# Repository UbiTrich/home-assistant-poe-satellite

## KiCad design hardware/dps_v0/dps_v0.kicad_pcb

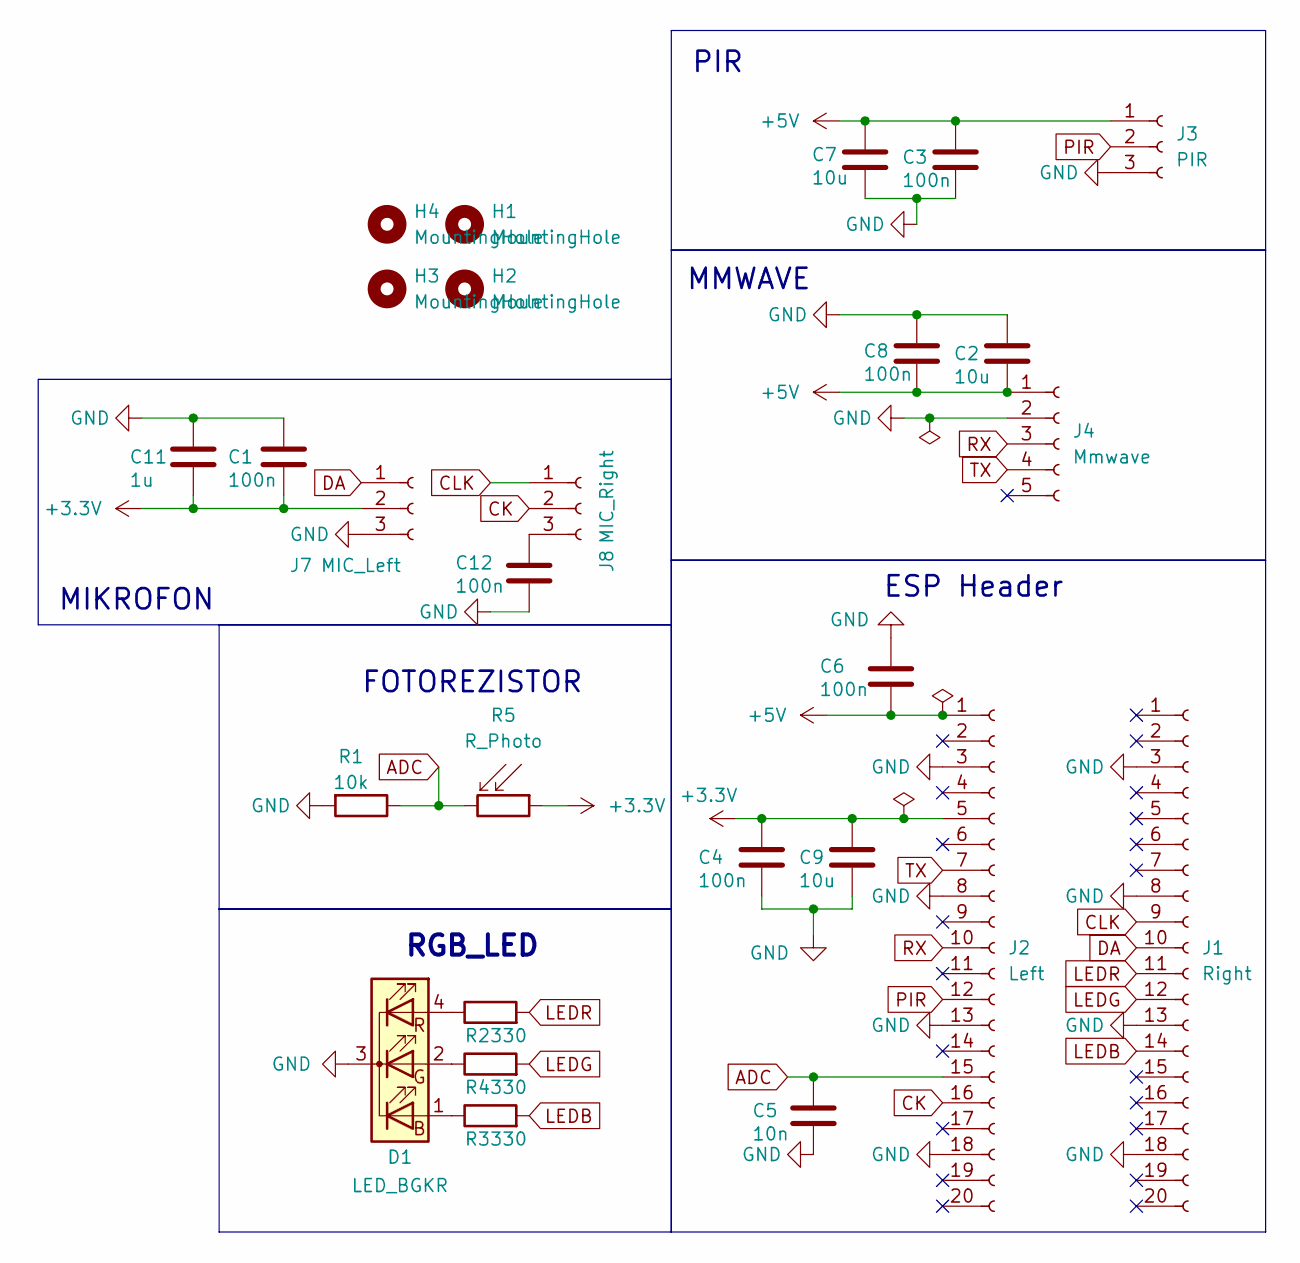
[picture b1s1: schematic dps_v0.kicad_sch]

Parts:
C1, C3, C4, C6, C8, C12: 100n; C_0805_2012Metric_Pad1.18x1.45mm_HandSolder
C2, C7, C9: 10u; C_0805_2012Metric_Pad1.18x1.45mm_HandSolder
C5: 10n; C_0805_2012Metric_Pad1.18x1.45mm_HandSolder
C11: 1u; C_0805_2012Metric_Pad1.18x1.45mm_HandSolder
D1: LED_BGKR; LED_D5.0mm-4_RGB_Wide_Pins
H1, H2, H3, H4: MountingHole; MountingHole_3mm
J1: Right; PinSocket_1x20_P2.54mm_Vertical
J2: Left; PinSocket_1x20_P2.54mm_Vertical
J3: PIR; PinSocket_1x03_P2.54mm_Vertical
J4: Mmwave; PinSocket_1x05_P1.27mm_Vertical
J7: MIC_Left; PinSocket_1x03_P2.54mm_Vertical
J8: MIC_Right; PinSocket_1x03_P2.54mm_Vertical
R1: 10k; R_0805_2012Metric_Pad1.20x1.40mm_HandSolder
R2, R3, R4: 330; R_0805_2012Metric_Pad1.20x1.40mm_HandSolder
R5: R_Photo; R_LDR_5.1x4.3mm_P3.4mm_Vertical

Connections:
+3.3V: C1.1, C4.2, C9.2, C11.1, J2.5, J7.2, R5.1
+5V: C2.1, C3.2, C6.1, C7.2, C8.1, J2.1, J3.1, J4.1
ADC: C5.2, J2.15, R1.1, R5.2
CK: J2.16, J8.2
CLK: J1.9, J8.1
DA: J1.10, J7.1
GND: C1.2, C2.2, C3.1, C4.1, C5.1, C6.2, C7.1, C8.2, C9.1, C11.2, C12.1, D1.3 (K), J1.3, J1.8, J1.13, J1.18, J2.3, J2.8, J2.13, J2.18, J3.3, J4.2, J7.3, R1.2
LEDB: J1.14, R3.2
LEDG: J1.12, R4.2
LEDR: J1.11, R2.2
unnamed: D1.1 (BA), R3.1
unnamed: D1.2 (GA), R4.1
unnamed: D1.4 (RA), R2.1
unnamed: C12.2, J8.3
PIR: J2.12, J3.2
RX: J2.10, J4.3
TX: J2.7, J4.4

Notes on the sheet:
ESP Header
MMWAVE
FOTOREZISTOR
MIKROFON
RGB_LED
PIR

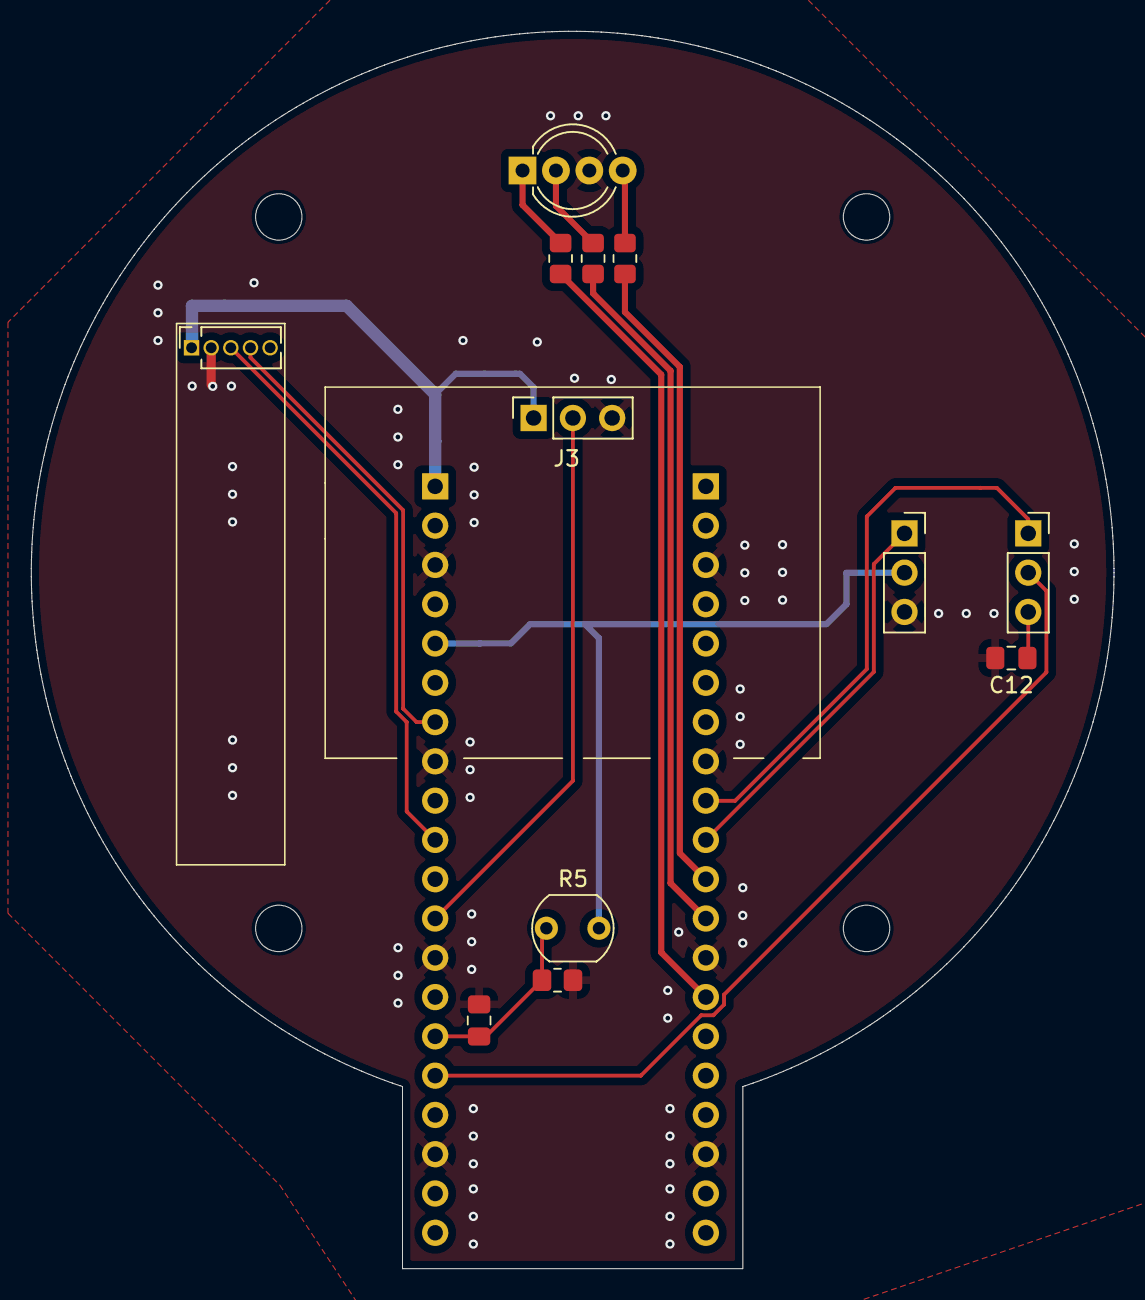
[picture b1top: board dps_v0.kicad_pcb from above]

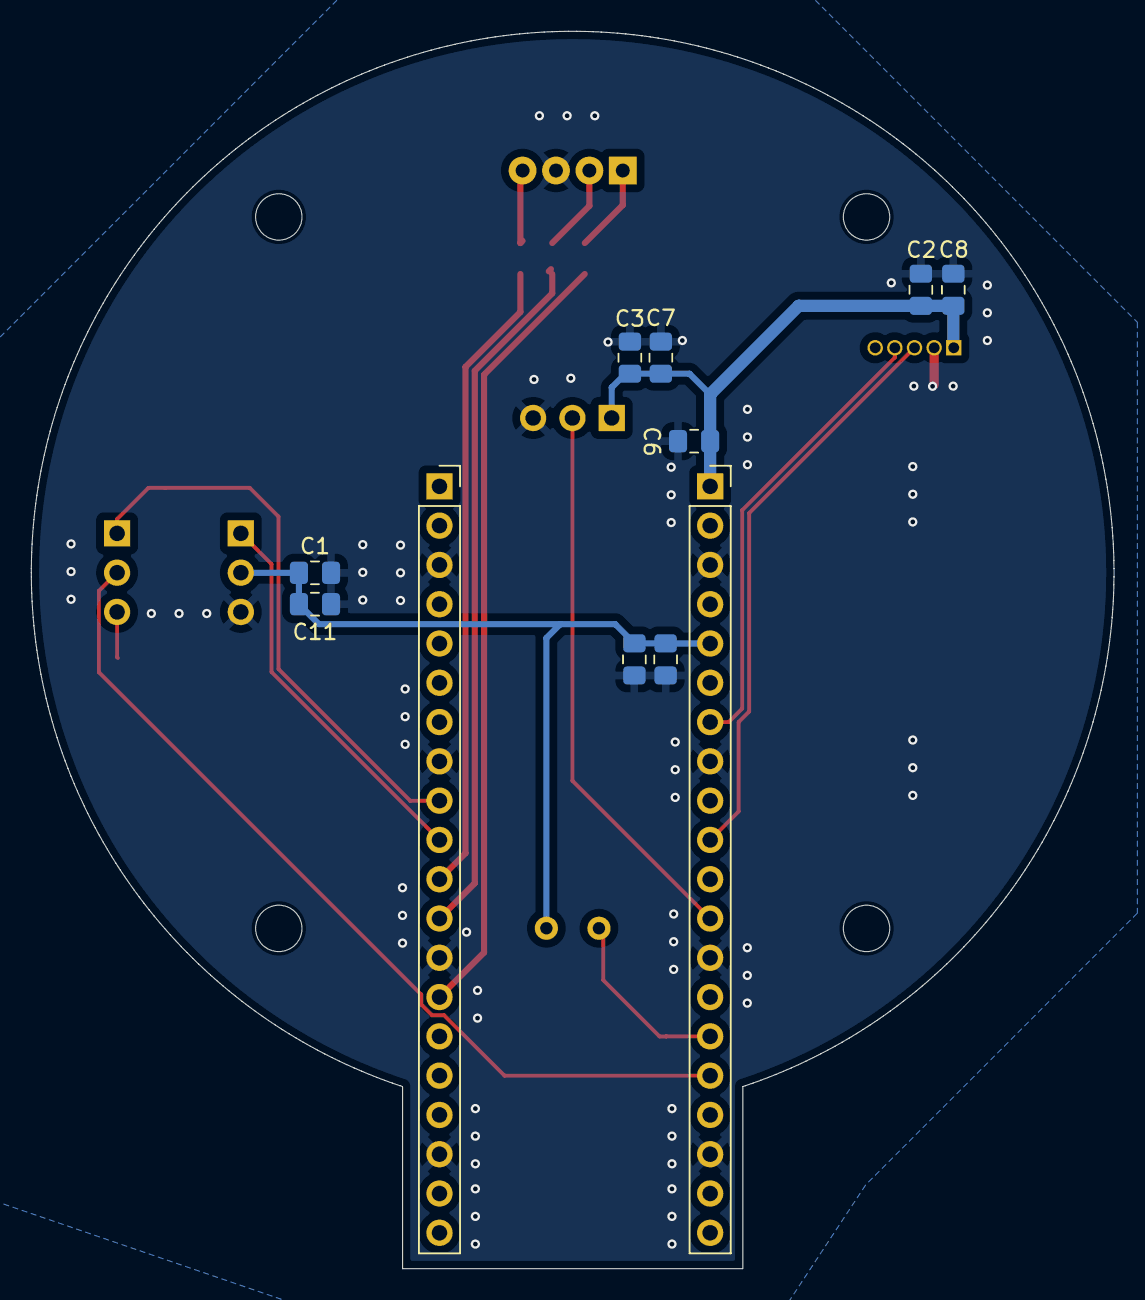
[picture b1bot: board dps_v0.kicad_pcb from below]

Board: 2 copper layers, 70.0 x 80.0 mm, 27 parts (11 on the bottom side), 17 nets.

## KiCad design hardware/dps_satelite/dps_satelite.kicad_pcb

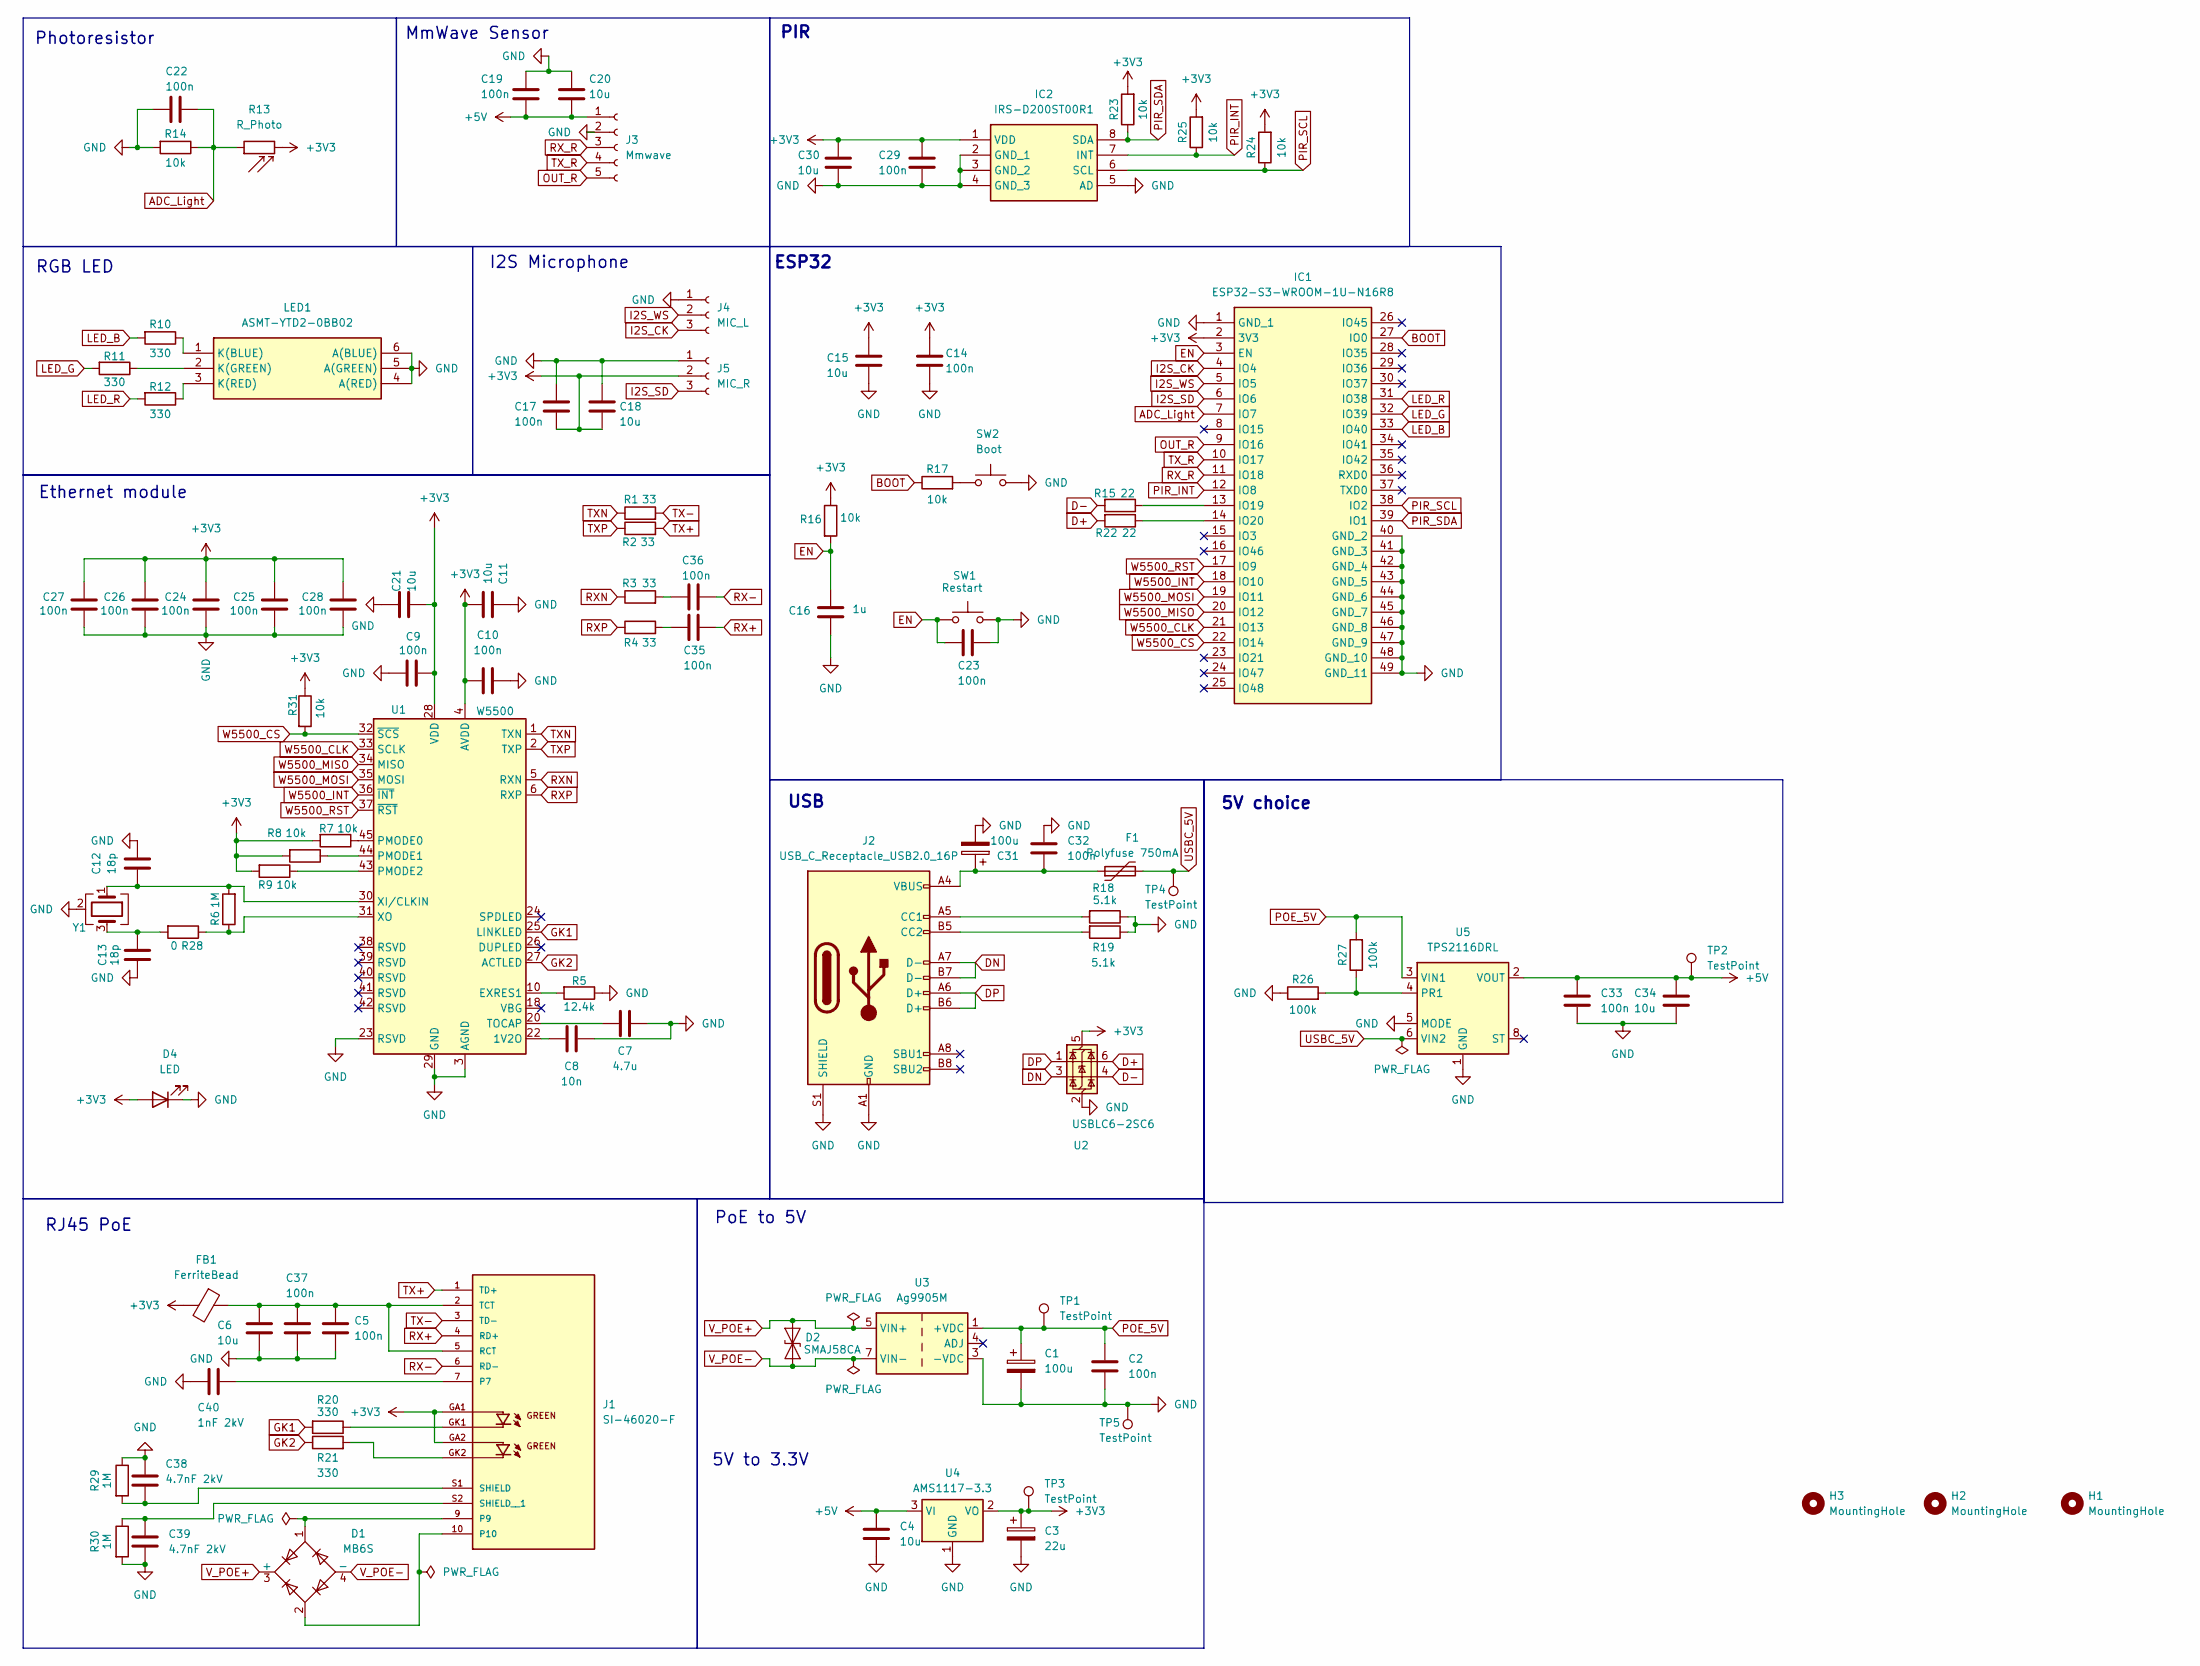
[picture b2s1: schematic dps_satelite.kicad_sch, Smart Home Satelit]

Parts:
C1, C31: 100u; CP_Elec_6.3x7.7
C2, C5, C9, C10, C14, C17, C19, C22, C23, C24, C25, C26, C27, C28, C29, C32, C33, C35, C36, C37: 100n; C_0603_1608Metric_Pad1.08x0.95mm_HandSolder
C3: 22u; CP_EIA-3216-10_Kemet-I_HandSolder
C4, C6, C15, C18, C20, C30, C34: 10u; C_0603_1608Metric_Pad1.08x0.95mm_HandSolder
C7: 4.7u; C_1206_3216Metric_Pad1.33x1.80mm_HandSolder
C8: 10n; C_0603_1608Metric_Pad1.08x0.95mm_HandSolder
C11, C21: 10u; C_0805_2012Metric_Pad1.18x1.45mm_HandSolder
C12, C13: 18p; C_0603_1608Metric_Pad1.08x0.95mm_HandSolder
C16: 1u; C_0603_1608Metric_Pad1.08x0.95mm_HandSolder
C38, C39: 4.7nF 2kV; C_0603_1608Metric_Pad1.08x0.95mm_HandSolder
C40: 1nF 2kV; C_0603_1608Metric_Pad1.08x0.95mm_HandSolder
D1: MB6S; TO-269AA
D2: SMAJ58CA; D_SMA
D4: LED; LED_1206_3216Metric
F1: Polyfuse 750mA; Fuse_0805_2012Metric
FB1: FerriteBead; C_0805_2012Metric_Pad1.18x1.45mm_HandSolder
H1, H2, H3: MountingHole; MountingHole_4.3mm_M4
IC1: ESP32-S3-WROOM-1U-N16R8; ESP32S3WROOM1UN16R8; Mouser Part Number 356-ESP32S3WM1UN16R8
IC2: IRS-D200ST00R1; IRSD200ST00R1; Manufacturer_Part_Number IRS-D200ST00R1
J1: SI-46020-F; BEL_SI-46020-F; PARTREV C
J2: USB_C_Receptacle_USB2.0_16P; MOLEX_2171820001
J3: Mmwave; PinSocket_1x05_P1.27mm_Vertical
J4: MIC_L; PinHeader_1x03_P2.54mm_Vertical_SMD_Pin1Right
J5: MIC_R; PinHeader_1x03_P2.54mm_Vertical_SMD_Pin1Right
LED1: ASMT-YTD2-0BB02; ASMTYTD20BB02; Mouser Part Number 630-ASMT-YTD2-0BB02
R1, R2, R3, R4: 33; R_0603_1608Metric_Pad0.98x0.95mm_HandSolder
R5: 12.4k; R_0603_1608Metric_Pad0.98x0.95mm_HandSolder
R6, R29, R30: 1M; R_0603_1608Metric_Pad0.98x0.95mm_HandSolder
R7, R8, R9, R14, R16, R17, R23, R24, R25, R31: 10k; R_0603_1608Metric_Pad0.98x0.95mm_HandSolder
R10, R11, R12, R20, R21: 330; R_0603_1608Metric_Pad0.98x0.95mm_HandSolder
R13: R_Photo; R_LDR_5.1x4.3mm_P3.4mm_Vertical
R15, R22: 22; R_0603_1608Metric_Pad0.98x0.95mm_HandSolder
R18, R19: 5.1k; R_0603_1608Metric_Pad0.98x0.95mm_HandSolder
R26, R27: 100k; R_0603_1608Metric_Pad0.98x0.95mm_HandSolder
R28: 0; R_0603_1608Metric_Pad0.98x0.95mm_HandSolder
SW1: Restart; SW_Tactile_SPST_NO_Straight_CK_PTS636Sx25SMTRLFS
SW2: Boot; SW_Tactile_SPST_NO_Straight_CK_PTS636Sx25SMTRLFS
TP1, TP2, TP3, TP4, TP5: TestPoint; TestPoint_Pad_2.0x2.0mm
U1: W5500; LQFP-48_7x7mm_P0.5mm
U2: USBLC6-2SC6; SOT-23-6
U3: Ag9905M; Converter_DCDC_Silvertel_Ag99xxLP_THT
U4: AMS1117-3.3; SOT-223-3_TabPin2
U5: TPS2116DRL; SOT-583-8
Y1: Crystal_GND24; Crystal_SMD_3225-4Pin_3.2x2.5mm

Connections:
+3V3: C3.1, C9.2, C10.2, C11.2, C14.2, C15.1, C17.2, C18.2, C21.2, C24.2, C25.2, C26.2, C27.2, C28.2, C29.1, C30.1, D4.2 (A), FB1.2, IC1.2 (3V3), IC2.1 (VDD), J1.GA1, J1.GA2, J5.2, R7.2, R8.2, R9.2, R13.2, R16.1, R23.2, R24.2, R25.2, R31.1, TP3.1, U1.4 (AVDD), U1.8 (AVDD), U1.11 (AVDD), U1.15 (AVDD), U1.17 (AVDD), U1.21 (AVDD), U1.28 (VDD), U2.5 (VBUS), U4.2 (VO)
+5V: C4.1, C19.2, C20.2, C33.1, C34.1, J3.1, TP2.1, U4.3 (VI), U5.2 (VOUT), U5.7 (VOUT)
ADC_Light: C22.1, IC1.7 (IO7), R13.1, R14.1
BOOT: IC1.27 (IO0), R17.1
D+: R22.2, U2.6 (I/O1)
D-: R15.2, U2.4 (I/O2)
DN: J2.A7 (D-), J2.B7 (D-), U2.3 (I/O2)
DP: J2.A6 (D+), J2.B6 (D+), U2.1 (I/O1)
EN: C16.2, C23.1, IC1.3 (EN), R16.2, SW1.1
GK1: R20.2, U1.25 (LINKLED)
GK2: R21.1, U1.27 (ACTLED)
GND: C1.2, C2.2, C3.2, C4.2, C5.2, C6.2, C7.2, C8.2, C9.1, C10.1, C11.1, C12.1, C13.1, C14.1, C15.2, C16.1, C17.1, C18.1, C19.1, C20.1, C21.1, C22.2, C23.2, C24.1, C25.1, C26.1, C27.1, C28.1, C29.2, C30.2, C31.2, C32.1, C33.2, C34.2, C37.2, C38.1, C39.2, C40.2, D4.1 (K), IC1.1 (GND_1), IC1.40 (GND_2), IC1.41 (GND_3), IC1.42 (GND_4), IC1.43 (GND_5), IC1.44 (GND_6), IC1.45 (GND_7), IC1.46 (GND_8), IC1.47 (GND_9), IC1.48 (GND_10), IC1.49 (GND_11), IC2.2 (GND_1), IC2.3 (GND_2), IC2.4 (GND_3), IC2.5 (AD), J2.A1 (GND), J2.A12 (GND), J2.B1 (GND), J2.B12 (GND), J2.S1 (SHIELD), J3.2, J4.1, J5.1, LED1.4 (A(RED)), LED1.5 (A(GREEN)), LED1.6 (A(BLUE)), R5.1, R14.2, R18.1, R19.1, R26.1, R29.1, R30.2, SW1.2, SW2.2, TP5.1, U1.3 (AGND), U1.9 (AGND), U1.14 (AGND), U1.16 (AGND), U1.19 (AGND), U1.23 (RSVD), U1.29 (GND), U1.48 (AGND), U2.2 (GND), U3.3 (-VDC), U4.1 (GND), U5.1 (GND), U5.5 (MODE), Y1.2 (G), Y1.4 (G)
I2S_CK: IC1.4 (IO4), J4.3
I2S_SD: IC1.6 (IO6), J5.3
I2S_WS: IC1.5 (IO5), J4.2
LED_B: IC1.33 (IO40), R10.2
LED_G: IC1.32 (IO39), R11.2
LED_R: IC1.31 (IO38), R12.2
unnamed: C13.2, R28.2, Y1.3
unnamed: C31.1, C32.2, F1.1, J2.A4 (VBUS), J2.A9 (VBUS), J2.B4 (VBUS), J2.B9 (VBUS)
unnamed: C35.1, R4.2
unnamed: C36.1, R3.2
unnamed: IC1.13 (IO19), R15.1
unnamed: IC1.14 (IO20), R22.1
unnamed: C40.1, J1.7
unnamed: D1.1, J1.9
unnamed: D1.2, J1.10
unnamed: J1.GK1, R20.1
unnamed: J1.GK2, R21.2
unnamed: C5.1, C6.1, C37.1, FB1.1, J1.2 (TCT), J1.5 (RCT)
unnamed: C38.2, J1.S1 (SHIELD), R29.2
unnamed: C39.1, J1.S2 (SHIELD__1), R30.1
unnamed: J2.A5 (CC1), R18.2
unnamed: J2.B5 (CC2), R19.2
unnamed: LED1.1 (K(BLUE)), R10.1
unnamed: LED1.2 (K(GREEN)), R11.1
unnamed: LED1.3 (K(RED)), R12.1
unnamed: R17.2, SW2.1
unnamed: C8.1, U1.22 (1V2O)
unnamed: R5.2, U1.10 (EXRES1)
unnamed: R7.1, U1.45 (PMODE0)
unnamed: R8.1, U1.44 (PMODE1)
unnamed: R9.1, U1.43 (PMODE2)
unnamed: C7.1, U1.20 (TOCAP)
unnamed: C12.2, R6.2, U1.30 (XI/CLKIN), Y1.1
unnamed: R6.1, R28.1, U1.31 (XO)
unnamed: R26.2, R27.1, U5.4 (PR1)
OUT_R: IC1.9 (IO16), J3.5
PIR_INT: IC1.12 (IO8), IC2.7 (INT), R25.1
PIR_SCL: IC1.38 (IO2), IC2.6 (SCL), R24.1
PIR_SDA: IC1.39 (IO1), IC2.8 (SDA), R23.1
POE_5V: C1.1, C2.1, R27.2, TP1.1, U3.1 (+VDC), U3.2 (+VDC), U5.3 (VIN1)
RX+: C35.2, J1.4 (RD+)
RX-: C36.2, J1.6 (RD-)
RXN: R3.1, U1.5 (RXN)
RXP: R4.1, U1.6 (RXP)
RX_R: IC1.11 (IO18), J3.3
TX+: J1.1 (TD+), R2.2
TX-: J1.3 (TD-), R1.2
TXN: R1.1, U1.1 (TXN)
TXP: R2.1, U1.2 (TXP)
TX_R: IC1.10 (IO17), J3.4
USBC_5V: F1.2, TP4.1, U5.6 (VIN2)
V_POE+: D1.3 (+), D2.2 (A2), U3.5 (VIN+), U3.6 (VIN+)
V_POE-: D1.4 (-), D2.1 (A1), U3.7 (VIN-), U3.8 (VIN-)
W5500_CLK: IC1.21 (IO13), U1.33 (SCLK)
W5500_CS: IC1.22 (IO14), R31.2, U1.32 (~SCS)
W5500_INT: IC1.18 (IO10), U1.36 (~INT)
W5500_MISO: IC1.20 (IO12), U1.34 (MISO)
W5500_MOSI: IC1.19 (IO11), U1.35 (MOSI)
W5500_RST: IC1.17 (IO9), U1.37 (~RST)

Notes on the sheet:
PoE to 5V
USB
MmWave Sensor
Ethernet module
5V choice
5V to 3.3V
RJ45 PoE
PIR
I2S Microphone
ESP32
Photoresistor
RGB LED

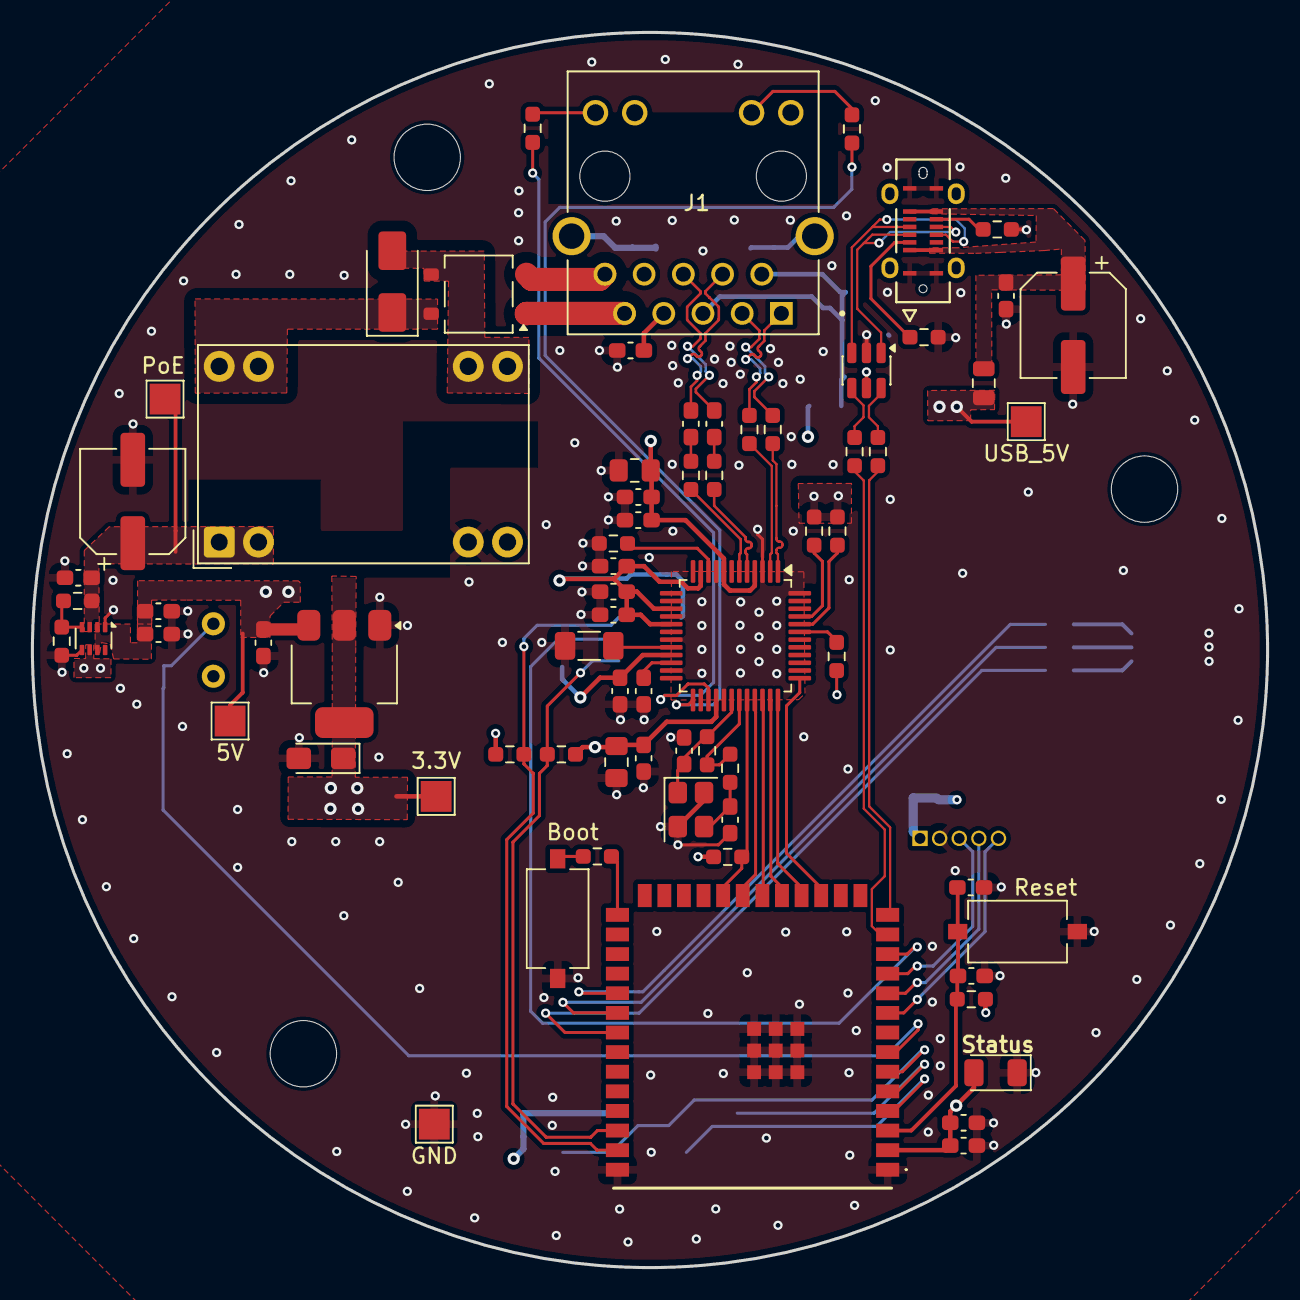
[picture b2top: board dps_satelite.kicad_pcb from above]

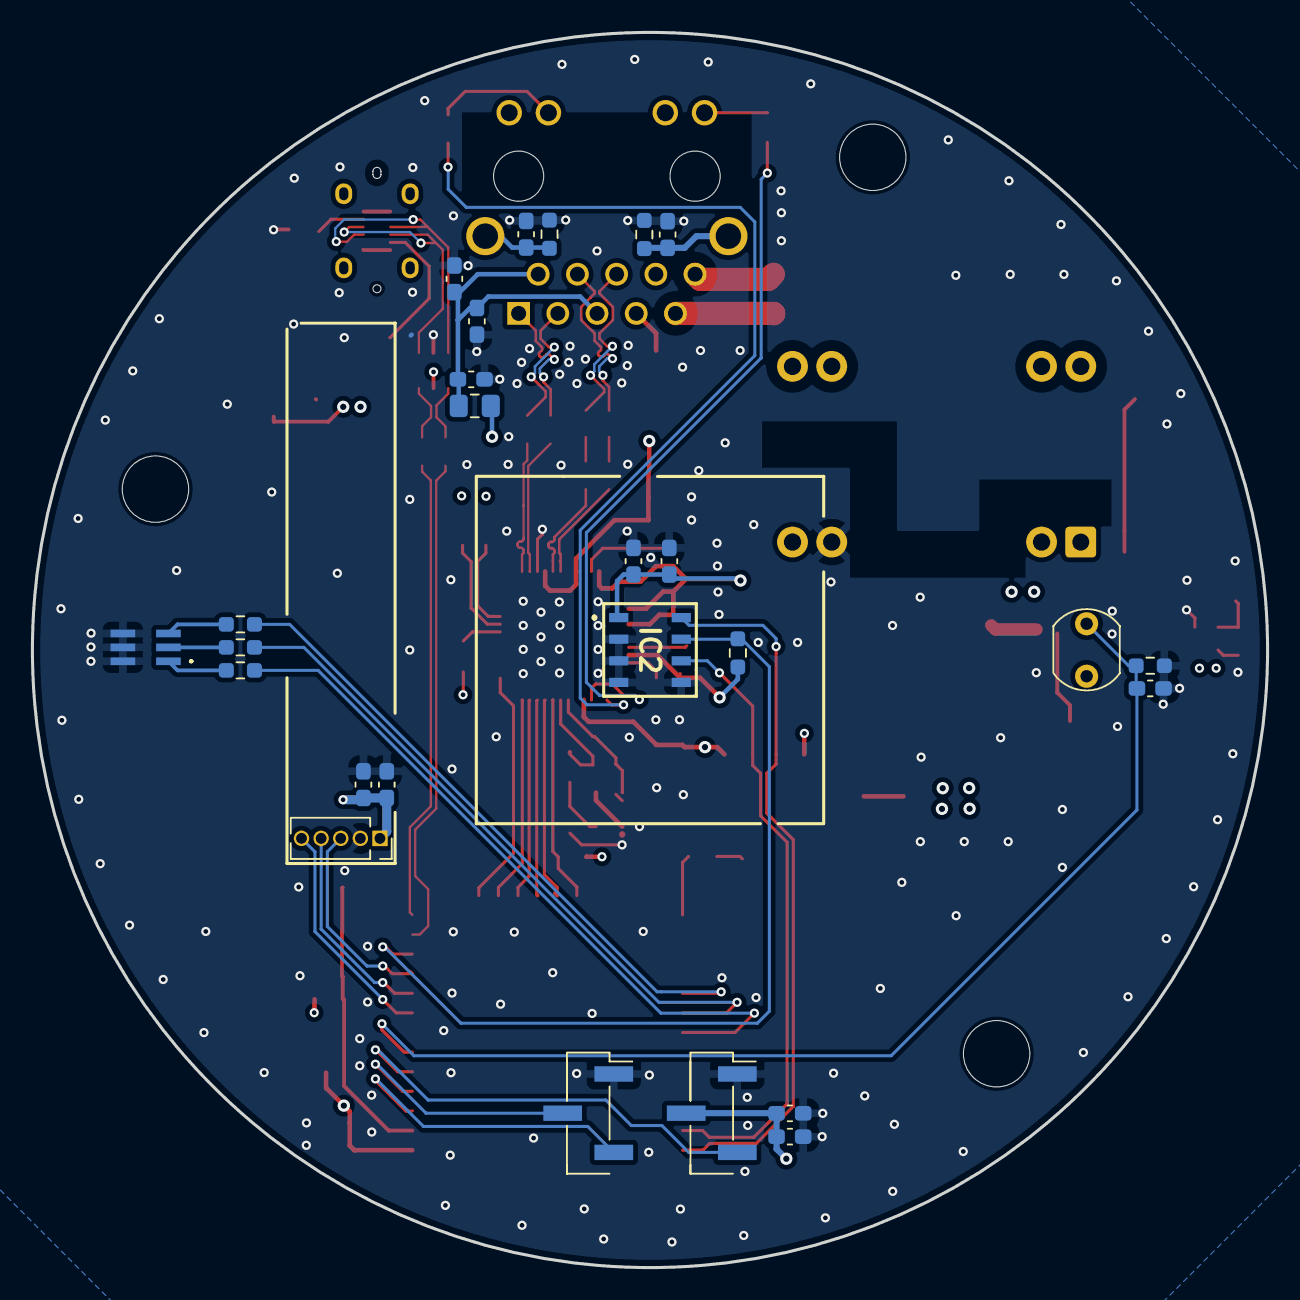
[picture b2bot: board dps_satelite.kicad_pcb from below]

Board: 4 copper layers, 80.0 x 80.0 mm, 100 parts (26 on the bottom side), 71 nets.

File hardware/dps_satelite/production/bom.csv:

Designator,Footprint,Quantity,Value,LCSC Part #
"C1, C31",CP_Elec_6.3x7.7,2,100u,
"C10, C14, C17, C19, C2, C22, C23, C24, C25, C26, C27, C28, C29, C32, C33, C35, C36, C37, C5, C9",0603,20,100n,
"C11, C21",0805,2,10u,
"C12, C13",0603,2,18p,
"C15, C18, C20, C30, C34, C4, C6",0603,7,10u,
C16,0603,1,1u,
C3,CP_EIA-3216-10_Kemet-I_HandSolder,1,22u,
C38,0603,1,4.7nF  2kV,
C39,0603,1,4.7nF 2kV,
C40,0603,1,1nF  2kV,
C7,1206,1,4.7u,
C8,0603,1,10n,
D1,TO-269AA,1,MB6S,
D2,D_SMA,1,SMAJ58CA,
D4,1206,1,LED,
F1,0805,1,Polyfuse 750mA,
FB1,0805,1,FerriteBead,
IC1,ESP32S3WROOM1UN16R8,1,ESP32-S3-WROOM-1U-N16R8,
IC2,IRSD200ST00R1,1,IRS-D200ST00R1,
J1,BEL_SI-46020-F,1,SI-46020-F,
J2,MOLEX_2171820001,1,USB_C_Receptacle_USB2.0_16P,
J3,PinSocket_1x05_P1.27mm_Vertical,1,Mmwave,
J4,PinHeader_1x03_P2.54mm_Vertical_SMD_Pin1Right,1,MIC_L,
J5,PinHeader_1x03_P2.54mm_Vertical_SMD_Pin1Right,1,MIC_R,
LED1,ASMTYTD20BB02,1,ASMT-YTD2-0BB02,
"R1, R2, R3, R4",0603,4,33,
"R10, R11, R12, R20, R21",0603,5,330,
R13,R_LDR_5.1x4.3mm_P3.4mm_Vertical,1,R_Photo,
"R14, R16, R17, R23, R24, R25, R31, R7, R8, R9",0603,10,10k,
"R15, R22",0603,2,22,
"R18, R19",0603,2,3k,
"R26, R27",0603,2,100k,
R28,0603,1,0,
"R29, R30, R6",0603,3,1M,
R5,0603,1,12.4k,
SW1,SW_Tactile_SPST_NO_Straight_CK_PTS636Sx25SMTRLFS,1,Restart,
SW2,SW_Tactile_SPST_NO_Straight_CK_PTS636Sx25SMTRLFS,1,Boot,
TP1,TestPoint_Pad_2.0x2.0mm,1,PoE,
TP2,TestPoint_Pad_2.0x2.0mm,1,5V,
TP3,TestPoint_Pad_2.0x2.0mm,1,3.3V,
TP4,TestPoint_Pad_2.0x2.0mm,1,USB_5V,
TP5,TestPoint_Pad_2.0x2.0mm,1,GND,
U1,LQFP-48_7x7mm_P0.5mm,1,W5500,
U2,SOT-23-6,1,USBLC6-2SC6,
U3,Converter_DCDC_Silvertel_Ag99xxLP_THT,1,Ag9905LP,
U4,SOT-223-3_TabPin2,1,AMS1117-3.3,
U5,SOT-583-8,1,TPS2116DRL,
Y1,Crystal_SMD_3225-4Pin_3.2x2.5mm,1,Crystal_GND24,

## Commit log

2026-05-22 Initial commit - hardware and firmware files
2026-05-22 murata_pir
2026-05-22 navod
2026-05-29 vO dps and raw code added
2026-06-05 Rename README.me.txt to README.md
2026-06-05 Fixed Navod
